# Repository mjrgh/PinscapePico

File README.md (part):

# 

Pinscape Pico is a comprehensive I/O controller for virtual pinball
cabinets, designed for the Raspberry Pi Pico RP2040.  It handles
nearly all of the common input and output functions in a virtual pin
cab: arcade-style pushbuttons and switches, accelerometer-based
nudging, mechanical plunger position sensing, and feedback effect
devices such as lights, shaker motors, fans, and solenoids.  It can be
used on a standalone Pico, and also with a wide range of peripheral
devices that expand the Pico's hardware capabilities: accelerometers,
PWM/LED driver chips, shift registers, GPIO expanders, ADCs, and
clock/calendar chips.  The project includes reference hardware designs for
several expansion boards that implement particular collections of
peripherals selected to meet the needs of most pin cab builders, and
all of the hardware interfaces are documented, so that you can design
your own custom boards if you prefer.

This project is a sequel to the original [Pinscape KL25Z controller](https://github.com/mjrgh/Pinscape_Controller),
but it's all new code, not a port of the KL25Z software.  The Pico is
a more powerful platform than the KL25Z, so I wanted to make a fresh
start to take advantage of the Pico's expanded capabilities.  Pinscape
Pico has all (I'm pretty sure) of the features of the original KL25Z
Pinscape, plus some neat new tricks.  It's a little more "technical"
than the KL25Z system, but also more powerful and flexible.

## Quick setup guide

A pre-built Windows installation is available on the github project page,
under the **Releases** section in the right panel.

The distribution is a ZIP file.  To install, just unpack the ZIP file
into a local directory on your hard disk.  Just about any folder
location will work, except that you should avoid any of the Windows
system folders and the C:\Program Files tree, since those folders
are protected.

Once you unpack the files, you can launch the Pinscape Pico GUI Config
Tool by double-clicking **GUIConfigTool.exe**.  That's designed to be
your main gateway to the system, and it'll display on-screen
instructions for setting up a new Pico with the Pinscape software.

[More setup details](#SetupDetails).

[Linux and MacOS versions](#linuxAndMac)

## What can you do with it?

Here are some examples of how you can set up a Pinscape Pico system.
There's a more comprehensive list of features a little later in this
article, but it might help to start with some more concrete examples
of what your overall system might look like.

* <b>Button controller:</b> A really simple way to use Pinscape is as
a button encoder, for connecting arcade pushbuttons to a PC.  The
Pico is the only piece of hardware you need for this (other than
the buttons), since you can connect the buttons directly to the Pico's
GPIO ports.  The Pico has a total of 26 external GPIO pins, so you can
connect up to 26 buttons.  Each button can be mapped to the PC as a
keyboard key, a gamepad button, or a variety of other options, and
the Pico responds to button presses within microseconds, for very small
latencies sending input to the PC.  (Pinscape can also handle many
more buttons than just 26 if you need more, but that gets a little
more complicated, because you have to add some external peripheral
chips to create more ports beyond the Pico's 26 built-in GPIO pins.)

* <b>Accelerometer-based nudge device:</b> A slightly more complex
setup adds an accelerometer, to detect when you nudge the cabinet, so
that the pinball simulator can apply the nudge force within the game.
Analog nudging adds a wonderful extra dimension to video pinball that
lets you interact with the game in a much more natural, physical way.
The Pico doesn't have a built-in accelerometer, so this setup
requires adding an external accelerometer.  But that's very easy
to do, thanks to breakout boards available from Adafruit, Sparkfun,
and others.  (A breakout board is a small circuit board with a
specific chip and all of the necessary supporting parts, fully
soldered and assembled, so all you need to do to connect it to a
Pico is run a few wires between the breakout board and the Pico
GPIO pins.)  I recommend the Adafruit MMA8451Q and LIS3DH boards
(MMA8451Q is the better choice in terms of sensor performance).
You can combine nudge input with button inputs, too, although this
will reduce the number of button ports to 24 (because the
accelerometer requires two GPIO ports for its own use).

* <b>Plunger:</b> You can also add a mechanical plunger position
sensor.  Apart from the plunger sensor itself, no other hardware
is needed.  The simplest plunger sensor type is a slide potentiometer,
which connects to the Pico with three wires.  You can combine this
with the accelerometer and button functions as well.

* <b>Feedback device controller:</b> Pinscape can act as a replacement
for the LedWiz and its competitors - devices that control a fixed set
of feedback devices, and do nothing else.  Pinscape can even emulate
the original LedWiz USB interface, if you want it to, which makes it
plug-and-play compatible with old LedWiz-based software.  To control
feedback devices, though, you need to add some custom external
hardware, because the Pico by itself can only control tiny amounts of
power, just enough for a small LED.  So you need "booster" (amplifier)
circuitry to control motors, solenoids, and bigger lights.  Pinscape
is flexible enough to work with a wide range of booster circuits, so
you can roll your own if you want, but you don't have to.  The
Pinscape Pico project includes several "reference" expansion board
designs, which are open-source circuit board layouts that anyone is
free to build on their own, or to customize to fit specific
requirements.

* <b>Comprehensive I/O controller:</b> The reference expansion boards
don't *just* control feedback devices.  They're designed as **all-in-one**
boards that handle just about everything you'd need in a full-featured pin
cab, including accelerometer, plunger, buttons, and feedback devices.
So you can combine the features of a button encoder, nudge device, and
feedback controller into a single Pico running Pinscape.

## Supported Pico versions

All of my development testing was done with a Raspberry Pi Pico RP2040
board.  There are numerous clones of the Pico available from different
vendors, but I haven't tested on any of those, so use those at your
own risk.  I don't mean to imply that other boards *won't* work, only
that I don't know one way or the other, since the only thing I've
actually tested against is the original Pico.  (There is one specific
problem that several people using unspecified clones have reported,
which is that saving configuration data to flash doesn't work on those
devices.  Since I've heard the same thing from a few people, it seems
to be a systematic problem with certain clones, but I don't know
specifically which devices are affected, since the clones are mostly
unbranded.  I don't know the cause of the problem, so if you run into
something like that with a clone, the only solution I can offer is to
switch to a genuine Raspberry Pi device.)

The release package also includes a build for the Raspberry Pi Pico2
RP2350.  The Pico 2 is a next-generation Pico with a new CPU, more
memory, and numerous upgrades to the on-board peripherals.  It looks
just like an original Pico, but it's really a whole new platform, and
it's not directly compatible - it requires a separate build.  Pinscape
support on Pico 2 is still experimental: I haven't tested it on the
Pico 2 beyond the basics, so there are probably some incompatibilities
yet to be found.  But reports so far have been that most features are
working as expected.  Note that there's no particular advantage to
running Pinscape on a Pico 2 over an original Pico, since the software
doesn't currently use any of the Pico 2's new features.

The Pico "W" variations (Pico W and Pico 2W) are **not supported** at
the moment.  The W's have somewhat different internal wiring to accommodate
the addition of the radio modules, and those wiring changes require some
corresponding software changes, which Pinscape doesn't provide.  Some
people have reported that Pinscape *mostly* works on the W; the only
problem reported so far is that the on-board LED doesn't work.  So you
can use a W if you can live with the LED not working, and with any
other problems that might still be lurking.  But I don't see any
reason you'd want to, because Pinscape can't take any advantage of
the W's wireless features.  You're better off using a regular Pico
for Pinscape, and saving the Pico W for an application that actually
uses the WiFi or Bluetooth features.

## Features

* USB keyboard emulation, for button input mapping

* USB gamepad emulation, for button inputs, accelerometer, and plunger

* XBox controller emulation ("XInput"), as an alternative to the HID gamepad
(and the controller's feedback features (LEDs and rumble motors) can be mapped to
output ports via the "computed output" feature)

* [Open Pinball Device](http://mjrnet.org/pinscape/OpenPinballDevice/OpenPinballDeviceHID.htm) support

* All input devices (keyboard, gamepad, XBox, Open Pinball Device) are optional, they can be mixed
and matched in any combination, and and all of their virtual controls (buttons,
joystick axes) can be individually mapped to whichever physical inputs you like
(physical buttons, accelerometer axes, plunger sensor)

* Support for PWM outputs directly through Pico GPIO ports, as well as
multiple external PWM output controller chips (TLC5940, TLC5947, TLC59116,
PCA9685), and even shift-register chips (74HC595)

* Gamma correction option for PWM output ports, with the gamma
calculated at the device's full resolution (e.g., 12-bit gamma scaling for
TLC5940, TLC5947, and PCA9685)

* Configurable "flipper logic" timer protection (in software) for all output ports

* Support for shift register output ports via 74HC595, which can be configured
as digital ON/OFF outputs or as PWM outputs

* Support for digital ON/OFF output ports via PCA9555 GPIO expander chips

* A companion project, "PWMWorker", turns additional Picos into 24-port
I2C PWM controllers, the equivalent of 1&half; TLC59116 or PCA9685
chips, but in the DIY-friendly Pico package, and at the DIY-friendly
Pico price point.  Add more PWM ports to your system, 24
at a time, without any SMD soldering.  
Details: [Data Sheet](http://mjrnet.org/pinscape/PWMWorker/DataSheet/PWMWorkerDataSheet.htm); [Project subtree](PWMWorker).

* Support for button inputs directly through Pico GPIO ports, as well as through
74HC165 shift registers and PCA9555 GPIO expanders

* Extremely low latency on GPIO and 74HC165 input ports (microseconds on the
device side, 1-2 milliseconds end-to-end delivery to the application through USB)

* Ports on PCA9555 chips can be individually assigned as button inputs ports and
feedback device output ports, freely mixing port types on the same chip

* An extensible design for all of the external hardware interfaces, to allow
new chips to be added in the future

* "Logical button" design that allows mapping multiple types of physical inputs to
multiple types of PC inputs and other actions, including keyboard keys, gamepad buttons,
IR remote control code transmissions, and internal actions such as engaging Night Mode
or firing an output port

* Button macros, to carry out a timed series of actions when a button (physical or logical) is pressed

* "Shift buttons", to allow mapping multiple functions to a single physical input; multiple
shift buttons can be defined, to allow for shift "chords" (analogous to PC key combinations like Shift+Ctrl+X)

* Short-press/long-press buttons, to map two functions to one button based on press time

* Native DOF support, via Pinscape Pico device recognition in DOF (present in unified R3++ DOF releases since late 2024)

* "Logical output port" design that allows mapping physical outputs to DOF ports, internal sources,
and "computed" sources that let you combine DOF ports, control multiple things with one DOF port,
control ports based on timed events or internal device events, and all sorts of other things

* Shared DOF output ports, for sharing a small number of physical feedback devices with a
larger set of virtual DOF ports, ideal for setting up a mini-cab with limited space

* Night Mode, to disable designated outputs as a group for quieter play

* Time-of-day features, and support for an external real-time clock (RTC) chip to keep time
while the power is off

* [LedWiz emulation](LedWizEmulationOptions.md), for legacy applications that access the LedWiz directly (rather than through DOF);

* IR remote control receiver/transmitter, with the full universal-learning-remote design from the KL25Z Pinscape

* The "TV ON" feature from the KL25Z Pinscape, with support for the same type of external power-sensing circuit,
and the same support for a TV Relay and IR command activation when a power-on transition occurs

* Plunger sensor support for all of the KL25Z Pinscape sensors, with the same plunger logic features

* Nudging, with support for multiple accelerometer chips (MMA8451Q, LIS3DH, LIS3DSH, MXC6655XA, MC3416, MPU-6050),
with an extensible design to allow support for more accelerometer chips to be added in the future

* Nudge Velocity input support for the latest Visual Pinball

* Plunger and accelerometer inputs can be mapped to any suitable gamepad axes, and can also be used
as inputs to logical buttons and logical output ports; for example, you can set up a button that
triggers when the accelerometer X axis exceeds a given threshold, or set up an LED that turns on
when the plunger is pulled

* Plunger Velocity input support for the latest Visual Pinball

* Extremely flexible configuration system, with practically all of the
hardware setup under user control, using the human-friendly JSON text file format

* Detailed error/status logging, viewable on the PC via UART (physical serial port), USB CDC (virtual COM port),
and the Config Tool, for easier troubleshooting

* A simple command console, accessible through UART and USB CDC ports, with access to internal
debugging and troubleshooting commands; mostly a debugging tool for developers, but possibly useful
for troubleshooting problems that don't easily yield to other means

* GUI configuration and testing tool, with detailed visualizations of hardware
and software status for button inputs, feedback device outputs, plunger sensor, and IR features

### Non-features (things Pinscape Pico doesn't do)

Pinscape Pico is billed as a "comprehensive" I/O controller for
virtual pinball cabinets, but there are a few I/O functions that
Pinscape doesn't handle.  In each case, the decision to omit them was
based primarily on the resource limits of the Pico: there would be too
many compromises trying to make a single Pico perform all of its
Pinscape duties *plus* these other tasks.  Fortunately, all of these
functions are already covered by other open-source projects that run
on similarly inexpensive hardware, so leaving them out of Pinscape
shouldn't be an obstacle to including them in a DIY pin cab.

* **No smart light strips:** Pinscape doesn't control smart light
strips - the kind with individually addressable RGB LEDs, such as
WS2812B strips.  The resource limit that makes this impractical to
include in Pinscape is the Pico's relatively small number of GPIO
ports.  For a typical pin cab light strip setup, you'd need four to
eight GPIO ports dedicated to the light strips.  Pinscape needs almost
all of the GPIO ports to itself as it is.

* **No Dot-Matrix Displays (DMDs):** Pinscape also doesn't control the
128x32 dot-matrix display panels found in 1990s pinball machines, and
still popular in virtual pinball cabinets.  The main reason to
dedicate a separate controller to the DMD is that it requires a lot of
USB bandwidth, since the DMD is essentially a small video display.  A
separate device with its own USB port is the simplest way to ensure
plenty of bandwidth for everyone.

## Documentation

The documentation is a little thin so far, since I haven't yet updated
the [Pinscape Build Guide](http://mjrnet.org/pinscape/BuildGuideV2/BuildGuide.php)
to cover the Pico system.  A lot of the general pin cab material in the Build
Guide still applies equally well to Pinscape Pico, since most of it isn't at all
tied to the KL25Z or the original Pinscape software.  But the Build Guide also
has a lot of material that's specifically about how to build and set up the
original Pinscape KL25Z system, and so far I haven't written anything equivalent
for the new Pico software.

Here's what's I do have:

<b>[JSON Configuration Reference](http://mjrnet.org/pinscape/PinscapePico/Help/JSONConfigRef.html):</b>
This has the most comprehensive documentation on the firmware's
workings currently available.  It's in reference format, so it's
not a very good tutorial, but each of the major features has an
introductory section that explains how it works, including wiring
guides for most of the supported peripheral hardware devices.
    
When you're using the configuration editor in the Config Tool, the
editor keeps track of your editing location, and can take you straight
to the reference section on the topic you're currently editing.
At the upper right corner of the editor window, there's a link showing
the current JSON element, which automatically updates to match the
JSON at the text cursor position.  Click the link to open the
reference section for the current JSON element.

<b>[Config Tool help](http://mjrnet.org/pinscape/PinscapePico/Help/ConfigTool.htm):</b>  This documents the Config Tool in detail.
It's built into the Config Tool UI, and is also available online.

<b>[LIS3DH setup guide](Guides/LIS3DH-Setup.md):</b>  A tutorial guide
to setting up a LIS3DH accelerometer with a standalone Pico.  This will
probably be the most common initial setup for people who don't need the
Expansion Boards, so I wrote this guide to help get started.

## LED Status Codes

The Pico has a small green LED on top, which the Pinscape software uses
as a very coarse status indicator.  When everything is running properly,
the LED flashes slowly, about one second on and one second off.  When
the USB connection is interrupted, such as when the host PC is in sleep
mode, the LED shows a very short flash about every two seconds.  If the
LED isn't flashing at all (either stuck on or stuck off), the software
isn't working properly.

<b>Expansion board RGB:</b> If you're using one of the Expansion
Board designs, the board features a full-color RGB LED, which the
software uses to display a slightly more detailed status indication:

* Slow alternating Blue/Green: connected, running properly, plunger sensor calibrated (or no plunger configured)

* Slow alternating Green/Yellow: connected, running properly, plunger sensor not yet calibrated

* Two short yellow flashes every two seconds: waiting for host PC to establish the USB connection

* Two short red flashes every two seconds: USB connection interrupted (cable disconnected or data/protocol error communicating with the PC)

* One short green flash every two seconds: host PC is in sleep mode

* Blue on/off every half second: TV ON countdown in progress after system powered on

* Fast Blue flashes: TV ON feature is transmitting IR commands

* Fast alternating Red/Orange: Safe Mode is in effect

* Slow alternating Green/Dim Green: Factory Reset mode is in effect

* Solid Blue: Plunger calibration is in progress

* Fast Blue flashes: Plunger calibration button is being pressed (keep holding to activate calibration)

* Solid Violet: Nudge noise level calibration is in progress

## More details on installation

### Initial Pico firmware installation

The Pinscape Pico Config Tool guides you through the initial setup process for a new
device.  Just run the program and follow the on-screen instructions under the "New
Device Setup" section.

If you prefer to carry out the steps manually, without the Config Tool involved,
you can also use the standard, native Boot Loader procedure you'd use with any Pico
software:

* Unplug your Pico from USB (and all other power sources)

* Press **and hold** the button on top of the Pico while plugging it in, then release the button

* You should see the Pico appear on your Windows desktop as a virtual thumb drive

* Drag and drop **PinscapePico-pico.uf2** from the Pinscape folder onto the Pico virtual disk
(or use a COPY command in a DOS box)

The Pico should now automatically reboot into the Pinscape software.  If the
software is working properly, the little green LED on top of the Pico will
blink at about 1 Hz, and the device should appear as a Pinscape Pico unit
in the Config Tool.

After the initial install, you can install firmware updates directly
through the Config Tool without all of the manual steps.

### Configuration

This project's configuration setup is rather different from the KL25Z
Pinscape setup.  Instead of a graphical config tool, Pinscape Pico
uses a text file written in the widely-used JSON format.

The JSON file format and contents are documented in the Config Tool
help.  The Config Tool features an integrated text editor (based on
Scintilla) with JSON syntax-aware coloring and indenting, and
quick linking from the current editing location (based on live
syntax scanning) to the relevant documentation.

When you first fire up the GUI Config Tool and go to the Main
Configuration view, the program will offer a choice of initial
template configurations that you can use as a starting point.
The templates contain many examples of common configuration
elements, commented out, that you can un-comment and edit as
needed to add to your own configuration.

Alternatively, you can also send a config file to the Pico using the
command-line Config Tool, from a DOS box:

`ConfigTool --put-config MyConfig.json --reset`

Replace `MyConfig.json` with the actual name of your JSON file.  The
`--put-config` part installs your JSON file on the device.  The new
settings don't go into effect until you reboot the device, which is
why we also added `--reset` at the end.

### Linux and MacOS

A Pico running Pinscape can be plugged into a Linux or MacOS host just
as well as a Windows host, but that leaves the question of how you
configure it.  The original GUI Config Tool that's part of this
repository only runs on Windows, but fortunately, there are a couple
of options for Linux and MacOS users.

<b>Pinscape Cross:</b>
The best option is [Pinscape Cross](https://github.com/superhac/pinscape-cross/),
by superhac.  Pinscape Cross is an independent, full-featured implementation of
the GUI Config Tool that runs on Windows, Linux, and MacOS.

https://github.com/superhac/pinscape-cross/

<b>Linux command-line tool:</b>
In addition, there's a Linux version of the original command-line
Config Tool available.  You can build it via the shell script `./build_linux.sh`,
under [CmdLineConfigTool/Linux/](CmdLineConfigTool/Linux/).  Once that's built,
you can install a config file on the Pico with this command:

`./pinscape-config --put-config MyConfig.json --reset`

The command-line tool only has a subset of the functionality of the
GUI versions, but it can handle most of the core setup operations.
Its big limitation is that it doesn't have any of the interactive
visualization and testing tools that the GUI versions have, so it's
not as helpful for testing and troubleshooting.

### Firmware updates

You can update the firmware using the same procedure as the initial
install, by forcing the Pico into Boot Loader mode via the BOOTSEL
button and manually copying the new UF2 file.

But there's also an easier way.  Once Pinscape is installed, the
Config Tool can install firmware updates for you with a couple of
mouse clicks, with no need to physically unplug the Pico or fuss with
the BOOTSEL button.

In the GUI config tool, the main Overview window has controls for
updating the firmware.

To update the firmware from a DOS box, use the command-line config tool:

`ConfigTool --update PinscapePico-pico.uf2`

That automatically places the Pico into Boot Loader mode, copies
the specified UF2 file into its flash, and reboots the Pico to
launch the updated firmware.

## Safe Mode

Pinscape uses the Pico's hardware watchdog module to automatically
detect most software crashes.  The watchdog is essentially a hardware
timer that performs a power-cycle reboot on the Pico if the software
ever stops responding for more than a fraction of a second.  This is
an excellent way to detect software crashes, freezes, and other
problems that make the software stop functioning correctly, and in
most cases, it prevents the Pico from ever getting into a truly
unresponsive state.

When the hardware watchdog detects a crash, it reboots Pinscape into
Safe Mode.  Safe Mode runs the normal Pinscape firmware, but it
bypasses the usual JSON configuration file, and instead uses a
stripped-down configuration with a minimal number of features enabled.
The idea is that most crashes are caused by specific features in the
software, rather than by the core system software, so disabling most
of the optional features will allow the basic core software to run
without problems.

When Safe Mode is active, the Config Tool can connect to the Pico, and
you can inspect and edit the JSON configuration file.  You can also
use Safe Mode to install new firmware, if you're aware of a newer
firmware version that contains a fix for the crash.

If you suspect that the crash that led to Safe Mode activation was due
to a particular feature, you can use Safe Mode to edit the
configuration file and disable the suspect feature.  If you think it
was due to a setting, but you're not sure which one, you can
experiment with disabling features until you find the one responsible.

If you think the crash was purely random or sporadic, you can just
reboot the Pico and try again.  If the Pico keeps going back into Safe
Mode after each reboot, you probably will need to disable something in
the configuration to get back to normal operation.

By default, Safe Mode uses default "factory" settings for everything.
You can optionally create your own Safe Mode configuration file via
the Config Tool, in the Safe Mode Config window.  This works exactly
like the regular JSON configuration; it's just a separate JSON file
that's loaded instead of the regular one when Safe Mode is triggered.
The Safe Mode config file lets you enable specific features even when
in Safe Mode.  Naturally, you should minimize the features you enable
here, since the whole point is to create a minimal configuration that's
less likely to crash specifically because it doesn't enable many features.
I like to configure the ID information here to match the main configuration,
and also enable the UART ports, so that I can access the command console
for troubleshooting even when Safe Mode is active.

## Recovering a bricked Pico

First, you can't actually "brick" a Pico, in the sense of rendering it
permanently unrecoverable due to a software error.  But the Pinscape
software certainly can crash, and it can crash at startup, such that
it won't connect to the Config Tool long enough to let you perform an
update.  So the Pico might *appear* to be bricked.  Even this is
unlikely, because the Pico will automatically detect most crashes
and reboot itself into Safe Mode (see above), giving you access to
basic configuration functions.

In the event that Safe Mode doesn't kick in, it's *still* essentially
impossible to truly brick a Pico, thanks to the Pico's boot loader
being etched into inalterable hardware ROM.  No matter how badly the
software screws up, there's just no physical way that it can break
the ROM.  If the Pinscape software ever makes your Pico appear unresponsive,
you can always restore it to Boot Loader condition as follows:

* Disconnect the Pico from USB (and any other power sources)

* Press **and hold** the BOOTSEL button on top of the Pico while plugging in the USB cable

Holding the BOOTSEL button during a power cycle activates the Pico
boot loader, bypassing any software loaded in flash.  Since it's
impossible to erase the boot loader program itself (as it's stored in
unerasable ROM), and since the BOOTSEL button physically bypasses the
flash during the reset, there's nothing that a firmware program can do
to prevent this assertion of Boot Loader control, even if it were
deliberately trying to.

After you perform the BOOTSEL maneuver, the Pico should appear as a
virtual thumb drive on your Windows desktop.  You can now replace the
flash firmware by dragging the new .UF2 onto the Pico thumb drive.

For most programs, it would be enough at this point to reinstall the
firmware.  However, that's not necessarily good enough with Pinscape,
because Pinscape *also* stores your configuration file in the Pico's
flash memory, in a separate area from the program executable.  You
can fully reset the Pico to factory conditions using the Config
Tool, via the Device menu on the main Overview page, or via the
Boot Loader view, if the device is currently in Boot Loader mode.

## Expansion boards

Pinscape Pico will work on a completely stand-alone Pico, but for
a full virtual pin cab setup, you'll almost certainly want to add
some external peripherals to supplement the Pico's relatively
small complement of GPIO ports, and its lack of an on-board
accelerometer.

As part of the Pinscape Pico project, I've developed a few custom
"expansion boards" purpose-built for virtual pin cabs.  They're
all open-source designs that anyone can build; you can find the
EAGLE layouts in the [ExpansionBoards](ExpansionBoards) folder.

* **DIY-friendly expansion board set:**  A two-board set, designed
  to work together as a unit, providing a complete virtual pin cab
  I/O controller powerful enough for a high-end build with just
  about every toy known.  "DIY-friendly" means that it's designed
  entirely from parts that are easy to source and easy to solder
  by hand - it's meant to be something you can build yourself.

* **"Pro" expansion board:** An all-in-one board with a similar
  set of features to the DIY-friendly set, just with everything
  packed into a single board, thanks to the higher density made possible
  by fine-pitch SMD parts.  I call it the "Pro" board not because
  it's any better than the DIY board, but just because it's not the
  sort of thing most people would *want* to build by hand, thanks
  to the use of small SMD parts.  It's really only practical to assemble
  robotically, and that probably means that it will only be economical
  to produce in moderately large batches, like tens or hundreds or units.
  I expect that this will be an obstacle to DIYers, but one of our
  enterprising community members who's set up for retail sales might
  be able to build them and offer them for sale.  But even so, the
  "pro" isn't for "proprietary" - it's still an open-source design
  that you can build yourself, provided you have the means to work
  with the small SMD parts involved.

* **KL25Z adapter:** An adapter board that makes the Pico mimic
  a KL25Z, for use with the original Pinscape KL25Z expansion boards.
  This is designed for people that already have the KL25Z boards,
  and want to keep using them, but also want to upgrade to the new
  Pico software.  This is designed as a drop-in replacement for the
  KL25Z in your old setup.

But Pinscape Pico isn't limited to *my* expansion board designs.
The software was designed from the ground up to be fully configurable,
and has support for numerous peripheral options.  It doesn't make any
assumptions about which peripheral devices are present.  It'll work
just as well with other people's expansion board designs as with my
board designs.

## How to build the project from source code

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
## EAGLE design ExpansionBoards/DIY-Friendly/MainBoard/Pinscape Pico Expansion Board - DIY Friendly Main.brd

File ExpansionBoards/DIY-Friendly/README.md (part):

# Pinscape Pico - DIY-Friendly Expansion Board

This is an EAGLE design for a two-board expansion set for the Pinscape
Pico software.  Pinscape Pico is firmware for the Raspberry Pi Pico
that turns a Pico into a highly customizable I/O controller for
virtual pinball cabinets.

## Description

This board set is my second Pinscape Pico expansion board design.  The
first is an All-In-One board that packs everything you need for a
well-equipped pin cab onto one 10x16 cm board.  To achieve that kind
of density, that design uses tiny SMD (surface-mount) parts for just
about everything, some of which are too small even to handle with
tweezers.  It's not something you want to assemble by hand, unless
your other hobby is building Swiss watches from scratch; it's really
only feasible to build in a factory with a pick-and-place machine.
That's only cost-effective if you're going to order at least 50 or 100
units, so I expect that the all-SMD board will only be of interest to
our more entrepreneurially-minded community membe who might be
willing to order up a batch and offer them for retail sale.  That's
why I've taken to referring to that design as the "Pro" expansion
board.

But Pinscape has always been for DIYers.  My mission from the start
has been to make it possible to build high-end pin cabs without
depending on commercial devices, since we're such a niche hobby that
it's hard to get most commercial vendors to take us seriously as
customers.  So I didn't like the idea of only having a "Pro" design; I
also wanted to provide a DIY-friendly design that works with the new
software.  That meant designing another board using only parts that
are easy to solder by hand.

The result is this two-board expansion set.  It outfits the Pico with
a large set of physical input and output connections that let you
connect just about everything you'd find in a top-of-the-line pin cab,
from button inputs to feedback device outputs.  It has two main
design goals:

* It's comprehensive: it provides the extra peripherals required for
all of the Pinscape features (accelerometer, plunger input, button
input, feedback device control, IR remotes, TV ON power sensing), and
has ample button and feedback device ports to wire a fully decked out
pin cab

* It's DIY-friendly: it includes only through-hole parts that can
be easily soldered by hand

A third, lesser-but-still-important priority is to use common parts
that are widely available and are likely to remain in production for
many years.  The original Pinscape KL25Z boards are difficult to build
today because they depend on a few specific parts that are no longer
in production, most especially the KL25Z itself, but also the
TLC5940NT PWM chips.  I tried to avoid those sorts of dependencies as
much as possible in this design.  The biggest unique-part dependency
is the Pico itself, which is widely available and well supported by
Raspberry Pi.

Unlike the original Pinscape KL25Z expansion boards, where you were
encouraged to mix and match the Main, Power, and Chime boards in
different combinations to come up with a bespoke port layout, this
board set is designed as a One-Size-Fits-All solution.  There's no
provision to add a second or third power board, and there aren't any
optional add-on boards comparable to the Chime board.  The goal is
that the two boards have enough general-purpose ports between them
that no one would even want to add a third board - the two boards
should cover just about everything in a full-featured pin cab.

You can, however, use the main board all by itself.  I tried to
arrange things so that almost everything is on the main board, except
for the bulk of the output ports.  And even then, the main board has a
fair number of outputs.  If you use the main board on its own, you
still get the 16 flasher/strobe ports and 12 of the high-current MOSFET
outputs, plus all of the other I/O functions (buttons, accelerometer,
plunger connections, IR remote, TV ON).  The second board just adds 16
more high-current MOSFET outputs and the 32 mid-power lamp outputs,
plus the real-time clock chip, which most people won't especially miss.
If you don't need all of the extra output ports or the RTC, the main
board makes a perfectly good stand-alone controller.

My reason for using a less "modular" design than the old boards is
that I think the modularity ended up being a net negative: it added
flexibility, but at the cost of more complexity.  And I don't think
very many people took advantage of the flexibility - I think
practically everyone built one of the "standard" configurations,
either the Main + Power board combo, or a Main + Power + Chime set.
But everyone still had to go through the process of planning their
setup and then customizing their configuration settings once it was
built.  This time around, I figured that if everyone's going to build
the standard configuration anyway, let's make the standard configuration
so comprehensive that no one would really need other options.  It
simplifies the design, and it simplifies everyone's planning and
setup process.

## Features

* 32 button inputs, using shift register chips for extremely low latency
scans (order of 10 microseconds)

* Accelerometer (LIS3DH), installed via a pre-assembled module
available from Adafruit (no need to hand-solder the tiny SMD chip),
for nudge sensing

* An optional ADC (analog-to-digital converter, ADS1115), installed
via a pre-assembled module available from Adafruit, for high-precision
analog input from a potentiometer-based plunger (improving on the Pico's
mediocre built-in ADC)

* 28 MOSFET outputs for high-current feedback devices, such as motors,
solenoids, and standard LED strips

* 16 flasher/strobe ports for high-current LEDs, up to 1A per port,
for driving the 3W RGB LEDs typically used for flasher panels plus
a strobe LED

* 32 medium-current ports, up to 500mA per port, for driving almost
any sort of lamp (small incandescent or LED bulbs like those used in
lighted pushbuttons, small LEDs, large LEDs), relays and contactors,
and anything else that runs on less than 500mA

* All output ports have full PWM control, with configurable PWM
frequencies up to 65000 Hz

* Plunger input port, pin-compatible with the original Pinscape KL25Z
plunger port; just plug in your existing Pinscape plunger

* IR transmitter and receiver, with the sensor and transmitter on
small separate boards (connected to the main board with cables), so
that can be positioned anywhere in (or outside) the cabinet, to place
them in line-of-sight with the devices they're communicating with

* Power-sensing circuit for the Pinscape TV ON function (to help you
implement seamless one-button startup of the whole pin cab, even when
using TVs that don't remember their power state)

* Real-time clock/calendar chip with battery backup, for time-keeping
across Pico resets, even when the board is unpowered

## Board Design Files

Each board set consists of two sub-boards, titled **Main** and **Power**.
These two boards are designed to work together as a set.

Each sub-board design is contained in a pair of EAGLE files: **.sch** is the schematic,
and **.brd** is the physical board layout file.

The **.sch** file is a schematic, which is a special symbolic language
that electrical engineers use to describe the connections between
components in a circuit.  The symbology is more or less standardized,
so anyone with a basic knowledge of electronics should be able to read
it.  The schematic doesn't have any details on how the parts are laid
out physically, so it can't be used by itself to manufacture a board.
It's primarily for use by humans, to understand how the board works at
the electronic level.

The **.brd** file represents the complete physical layout of the
board.  This implements the same abstract network of connections
contained in the schematic, but it adds full details on the exact
physical placement of each component, and the layout of the copper
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
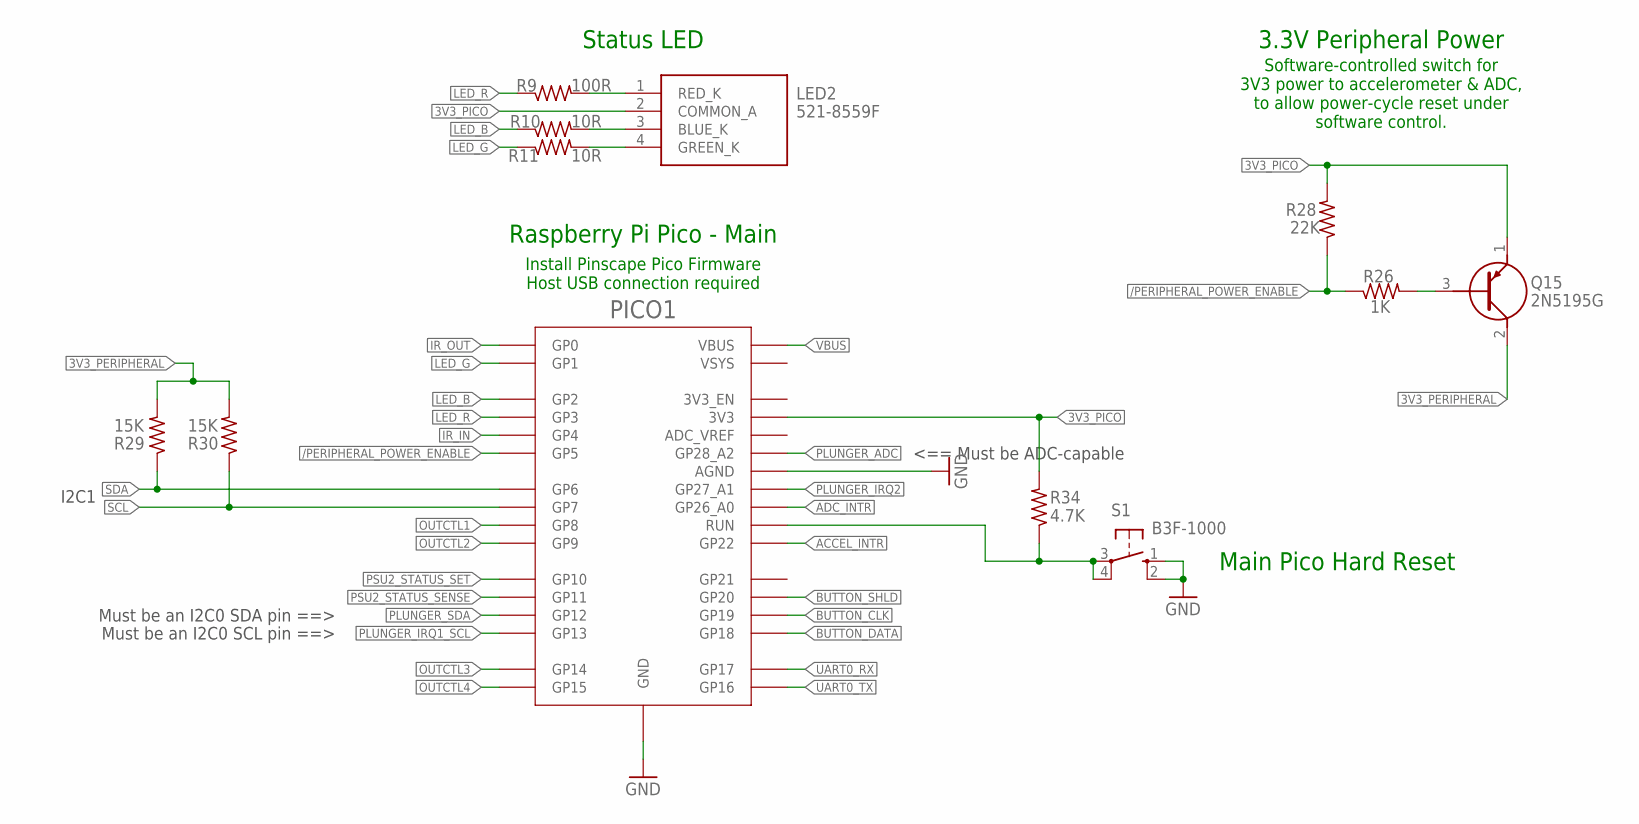
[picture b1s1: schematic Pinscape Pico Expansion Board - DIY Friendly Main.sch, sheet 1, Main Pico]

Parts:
LED2: 521-8559F; 5218559F
PICO1: RPI_PICO_NO_DEBUG; RPI_PICO_TH_NO_DEBUG
Q15: 2N5195G; TO229P300X760X1364-3P
R9: 100R; 0204/7; PARTNO MFR-12FTE52-100R
R10, R11: 10R; 0204/7; PARTNO MFR25SFTE52-10R
R26: 1K; 0204/7; PARTNO MF0204FTE52-1K
R28: 22K; 0204/7; PARTNO 660-MFS1/4DCT52R47R0
R29, R30: 15K; 0204/7; PARTNO MFR25SFRF52-15K
R34: 4.7K; 0204/7; PARTNO 660-MFS1/4DCT52R47R0
S1: B3F-1000; B3F-10XX

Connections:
3V3_PERIPHERAL: Q15.2 (C), R29.2, R30.2; also elsewhere on the board
3V3_PICO: LED2.2 (COMMON_A), PICO1.3V3, Q15.1 (E), R28.2, R34.2; also elsewhere on the board
/PERIPHERAL_POWER_ENABLE: PICO1.GP5, R26.1, R28.1; also elsewhere on the board
ACCEL_INTR: PICO1.GP22; also elsewhere on the board
ADC_INTR: PICO1.GP26_A0; also elsewhere on the board
BUTTON_CLK: PICO1.GP19; also elsewhere on the board
BUTTON_DATA: PICO1.GP18; also elsewhere on the board
BUTTON_SHLD: PICO1.GP20; also elsewhere on the board
GND: PICO1.AGND, PICO1.GND@1 (GND), PICO1.GND@2 (GND), PICO1.GND@3 (GND), PICO1.GND@4 (GND), PICO1.GND@6 (GND), PICO1.GND@7 (GND), PICO1.GND@8 (GND), S1.1 (S), S1.2 (S1); also elsewhere on the board
IR_IN: PICO1.GP4; also elsewhere on the board
IR_OUT: PICO1.GP0; also elsewhere on the board
LED_B: PICO1.GP2, R10.1
LED_G: PICO1.GP1, R11.1
LED_R: PICO1.GP3, R9.1
unnamed: LED2.1 (RED_K), R9.2
unnamed: Q15.3 (B), R26.2
unnamed: PICO1.RUN, R34.1, S1.3, S1.4 (P1)
unnamed: LED2.3 (BLUE_K), R10.2
unnamed: LED2.4 (GREEN_K), R11.2
OUTCTL1: PICO1.GP8; also elsewhere on the board
OUTCTL2: PICO1.GP9; also elsewhere on the board
OUTCTL3: PICO1.GP14; also elsewhere on the board
OUTCTL4: PICO1.GP15; also elsewhere on the board
PLUNGER_ADC: PICO1.GP28_A2; also elsewhere on the board
PLUNGER_IRQ1_SCL: PICO1.GP13; also elsewhere on the board
PLUNGER_IRQ2: PICO1.GP27_A1; also elsewhere on the board
PLUNGER_SDA: PICO1.GP12; also elsewhere on the board
PSU2_STATUS_SENSE: PICO1.GP11; also elsewhere on the board
PSU2_STATUS_SET: PICO1.GP10; also elsewhere on the board
SCL: PICO1.GP7, R30.1; also elsewhere on the board
SDA: PICO1.GP6, R29.1; also elsewhere on the board
UART0_RX: PICO1.GP17; also elsewhere on the board
UART0_TX: PICO1.GP16; also elsewhere on the board
VBUS: PICO1.VBUS; also elsewhere on the board

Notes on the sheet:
Raspberry Pi Pico - Main
Must be an I2C0 SCL pin ==>
<== Must be ADC-capable
Must be an I2C0 SDA pin ==>
Main Pico Hard Reset
Status LED
3.3V Peripheral Power
Install Pinscape Pico Firmware Host USB connection required
I2C1
Software-controlled switch for 3V3 power to accelerometer & ADC, to allow power-cycle reset under software control.

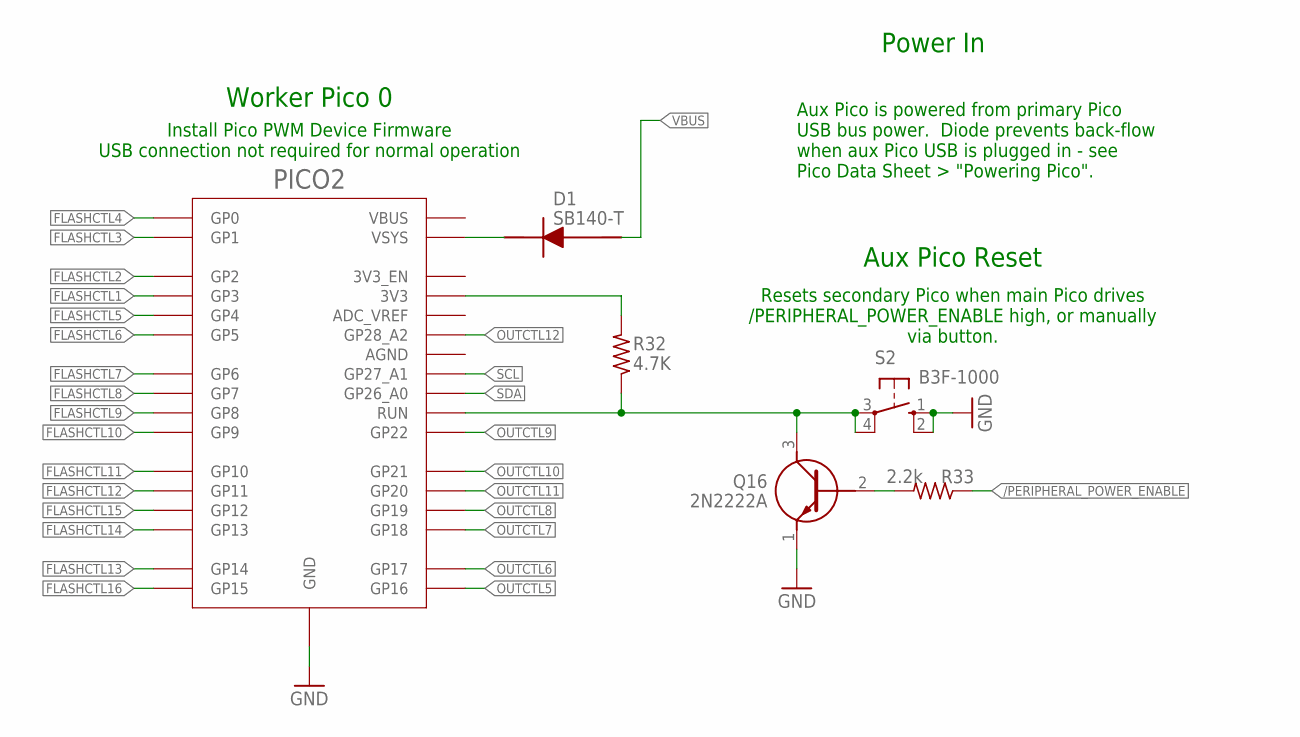
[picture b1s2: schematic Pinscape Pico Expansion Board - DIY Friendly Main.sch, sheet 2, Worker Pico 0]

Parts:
D1: SB140-T; DIOAD1408W86L464D236
PICO2: RPI_PICO_NO_DEBUG; RPI_PICO_TH_NO_DEBUG
Q16: 2N2222A
R32: 4.7K; 0204/7; PARTNO 660-MFS1/4DCT52R47R0
R33: 2.2k; 0204/7; PARTNO 660-MFS1/4DCT52R47R0
S2: B3F-1000; B3F-10XX

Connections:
/PERIPHERAL_POWER_ENABLE: R33.1; also elsewhere on the board
FLASHCTL1: PICO2.GP3; also elsewhere on the board
FLASHCTL2: PICO2.GP2; also elsewhere on the board
FLASHCTL3: PICO2.GP1; also elsewhere on the board
FLASHCTL4: PICO2.GP0; also elsewhere on the board
FLASHCTL5: PICO2.GP4; also elsewhere on the board
FLASHCTL6: PICO2.GP5; also elsewhere on the board
FLASHCTL7: PICO2.GP6; also elsewhere on the board
FLASHCTL8: PICO2.GP7; also elsewhere on the board
FLASHCTL9: PICO2.GP8; also elsewhere on the board
FLASHCTL10: PICO2.GP9; also elsewhere on the board
FLASHCTL11: PICO2.GP10; also elsewhere on the board
FLASHCTL12: PICO2.GP11; also elsewhere on the board
FLASHCTL13: PICO2.GP14; also elsewhere on the board
FLASHCTL14: PICO2.GP13; also elsewhere on the board
FLASHCTL15: PICO2.GP12; also elsewhere on the board
FLASHCTL16: PICO2.GP15; also elsewhere on the board
GND: PICO2.GND@1 (GND), PICO2.GND@2 (GND), PICO2.GND@3 (GND), PICO2.GND@4 (GND), PICO2.GND@6 (GND), PICO2.GND@7 (GND), PICO2.GND@8 (GND), Q16.1 (E), S2.1 (S), S2.2 (S1); also elsewhere on the board
unnamed: D1.1 (K), PICO2.VSYS
unnamed: Q16.2 (B), R33.2
unnamed: PICO2.3V3, R32.2
unnamed: PICO2.RUN, Q16.3 (C), R32.1, S2.3, S2.4 (P1)
OUTCTL5: PICO2.GP16; also elsewhere on the board
OUTCTL6: PICO2.GP17; also elsewhere on the board
OUTCTL7: PICO2.GP18; also elsewhere on the board
OUTCTL8: PICO2.GP19; also elsewhere on the board
OUTCTL9: PICO2.GP22; also elsewhere on the board
OUTCTL10: PICO2.GP21; also elsewhere on the board
OUTCTL11: PICO2.GP20; also elsewhere on the board
OUTCTL12: PICO2.GP28_A2; also elsewhere on the board
SCL: PICO2.GP27_A1; also elsewhere on the board
SDA: PICO2.GP26_A0; also elsewhere on the board
VBUS: D1.2 (A); also elsewhere on the board

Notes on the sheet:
Install Pico PWM Device Firmware USB connection not required for normal operation
Worker Pico 0
Aux Pico Reset
Resets secondary Pico when main Pico drives /PERIPHERAL_POWER_ENABLE high, or manually via button.
Aux Pico is powered from primary Pico USB bus power. Diode prevents back-flow when aux Pico USB is plugged in - see Pico Data Sheet > "Powering Pico".
Power In

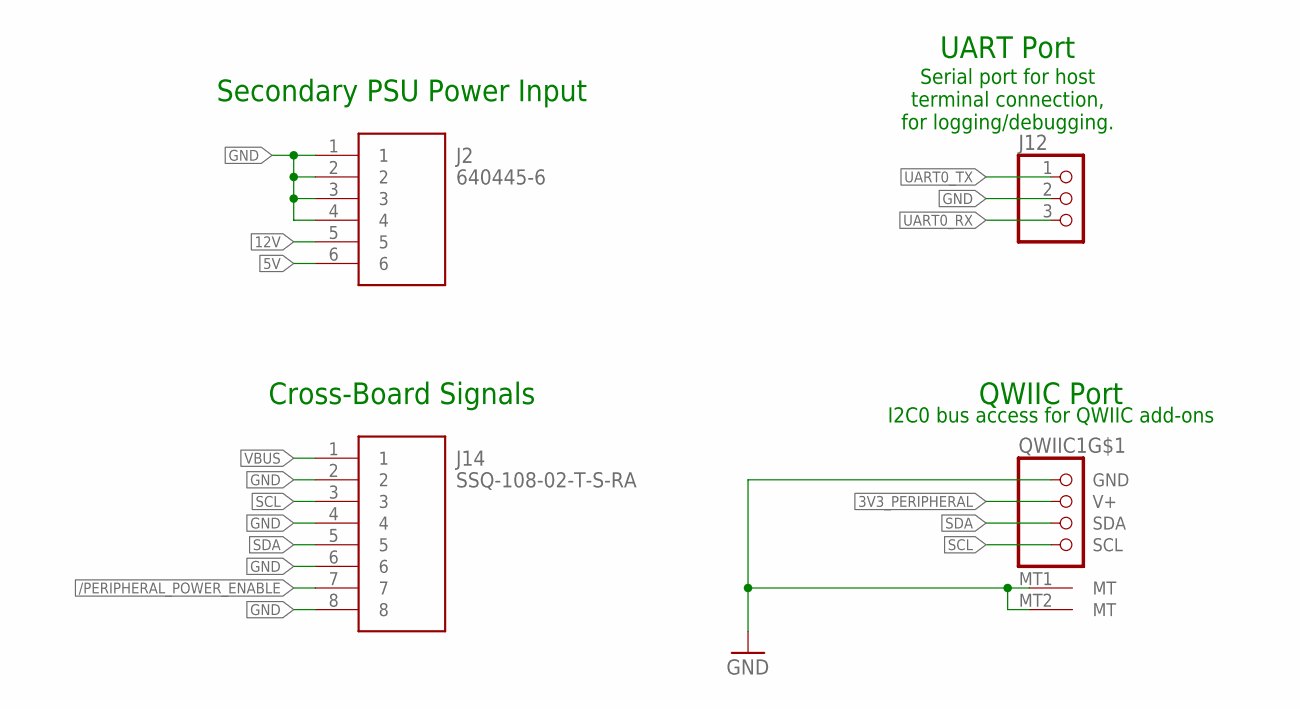
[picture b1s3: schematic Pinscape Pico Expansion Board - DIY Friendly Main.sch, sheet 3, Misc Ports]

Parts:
J2: 640445-6; SHDR6W183P0X396_1X6_2377X762X1
J12: PINHD-1X3; 1X03
J14: SSQ-108-02-T-S-RA; RHDRRA8W64P254_1X8_2083X851X24
QWIIC1: QWIIC; JST_SH4

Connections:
3V3_PERIPHERAL: QWIIC1.2 (V+); also elsewhere on the board
5V: J2.6; also elsewhere on the board
12V: J2.5; also elsewhere on the board
/PERIPHERAL_POWER_ENABLE: J14.7; also elsewhere on the board
GND: J2.1, J2.2, J2.3, J2.4, J12.2, J14.2, J14.4, J14.6, J14.8, QWIIC1.1 (GND), QWIIC1.MT1 (MT), QWIIC1.MT2 (MT); also elsewhere on the board
SCL: J14.3, QWIIC1.4 (SCL); also elsewhere on the board
SDA: J14.5, QWIIC1.3 (SDA); also elsewhere on the board
UART0_RX: J12.3; also elsewhere on the board
UART0_TX: J12.1; also elsewhere on the board
VBUS: J14.1; also elsewhere on the board

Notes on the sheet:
UART Port
Serial port for host terminal connection, for logging/debugging.
Secondary PSU Power Input
Cross-Board Signals
QWIIC Port
I2C0 bus access for QWIIC add-ons

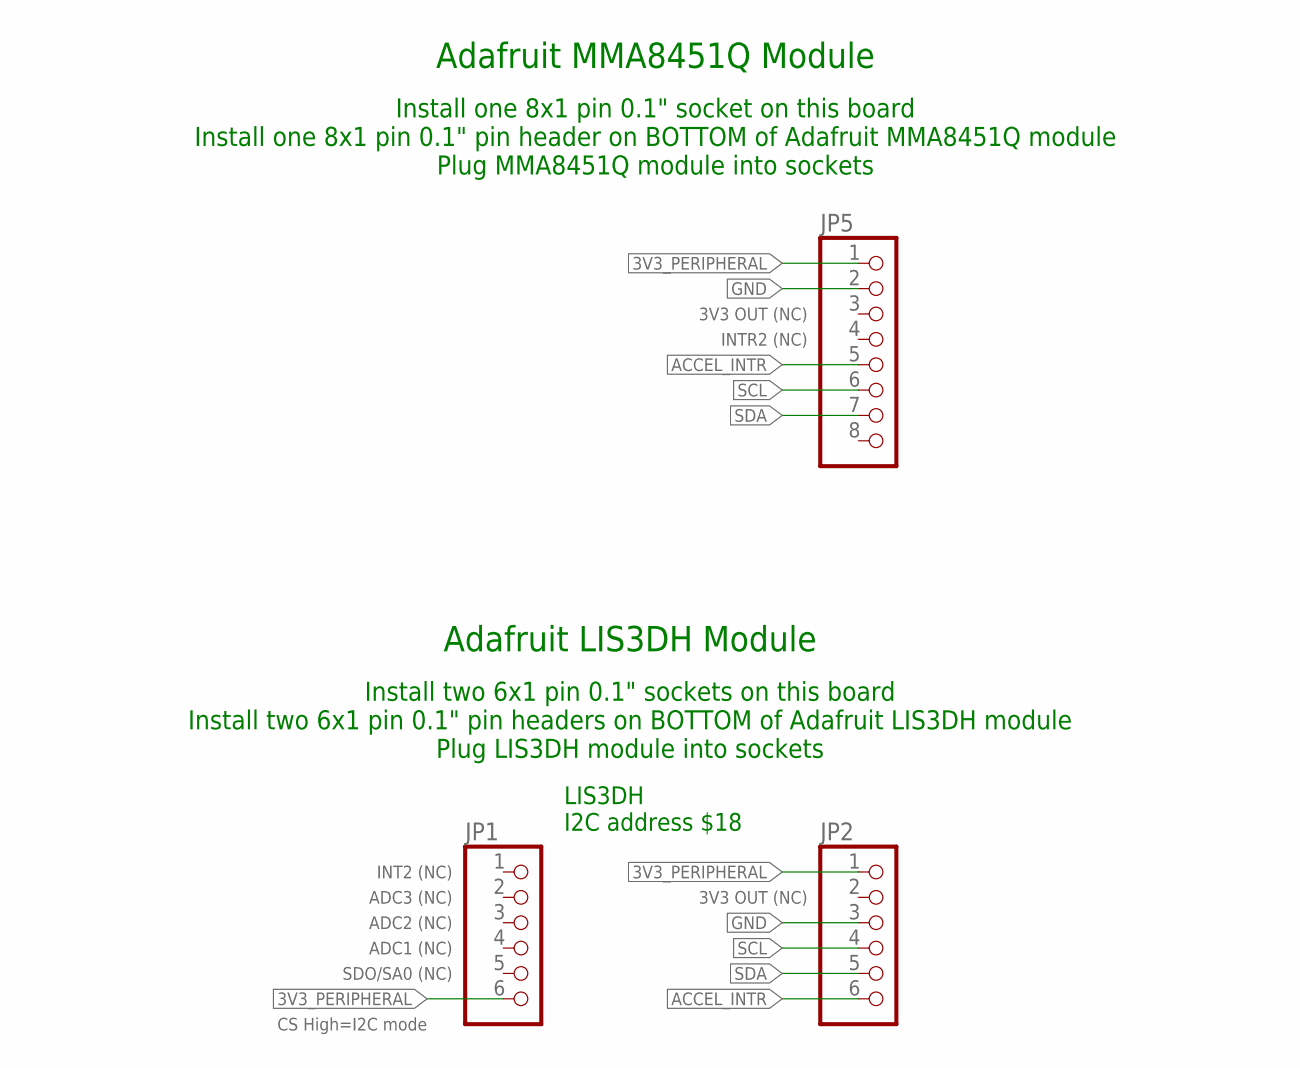
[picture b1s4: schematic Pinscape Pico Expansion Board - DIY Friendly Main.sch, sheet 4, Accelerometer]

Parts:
JP1, JP2: PINHD-1X6; 1X06
JP5: PINHD-1X8; 1X08

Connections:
3V3_PERIPHERAL: JP1.6, JP2.1, JP5.1; also elsewhere on the board
ACCEL_INTR: JP2.6, JP5.5; also elsewhere on the board
GND: JP2.3, JP5.2; also elsewhere on the board
SCL: JP2.4, JP5.6; also elsewhere on the board
SDA: JP2.5, JP5.7; also elsewhere on the board

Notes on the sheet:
Adafruit LIS3DH Module
Install two 6x1 pin 0.1" sockets on this board Install two 6x1 pin 0.1" pin headers on BOTTOM of Adafruit LIS3DH module Plug LIS3DH module into sockets
INT2 (NC)
ADC3 (NC)
ADC2 (NC)
ADC1 (NC)
SDO/SA0 (NC)
3V3 OUT (NC)
LIS3DH I2C address $18
CS High=I2C mode
Adafruit MMA8451Q Module
Install one 8x1 pin 0.1" socket on this board Install one 8x1 pin 0.1" pin header on BOTTOM of Adafruit MMA8451Q module Plug MMA8451Q module into sockets
INTR2 (NC)

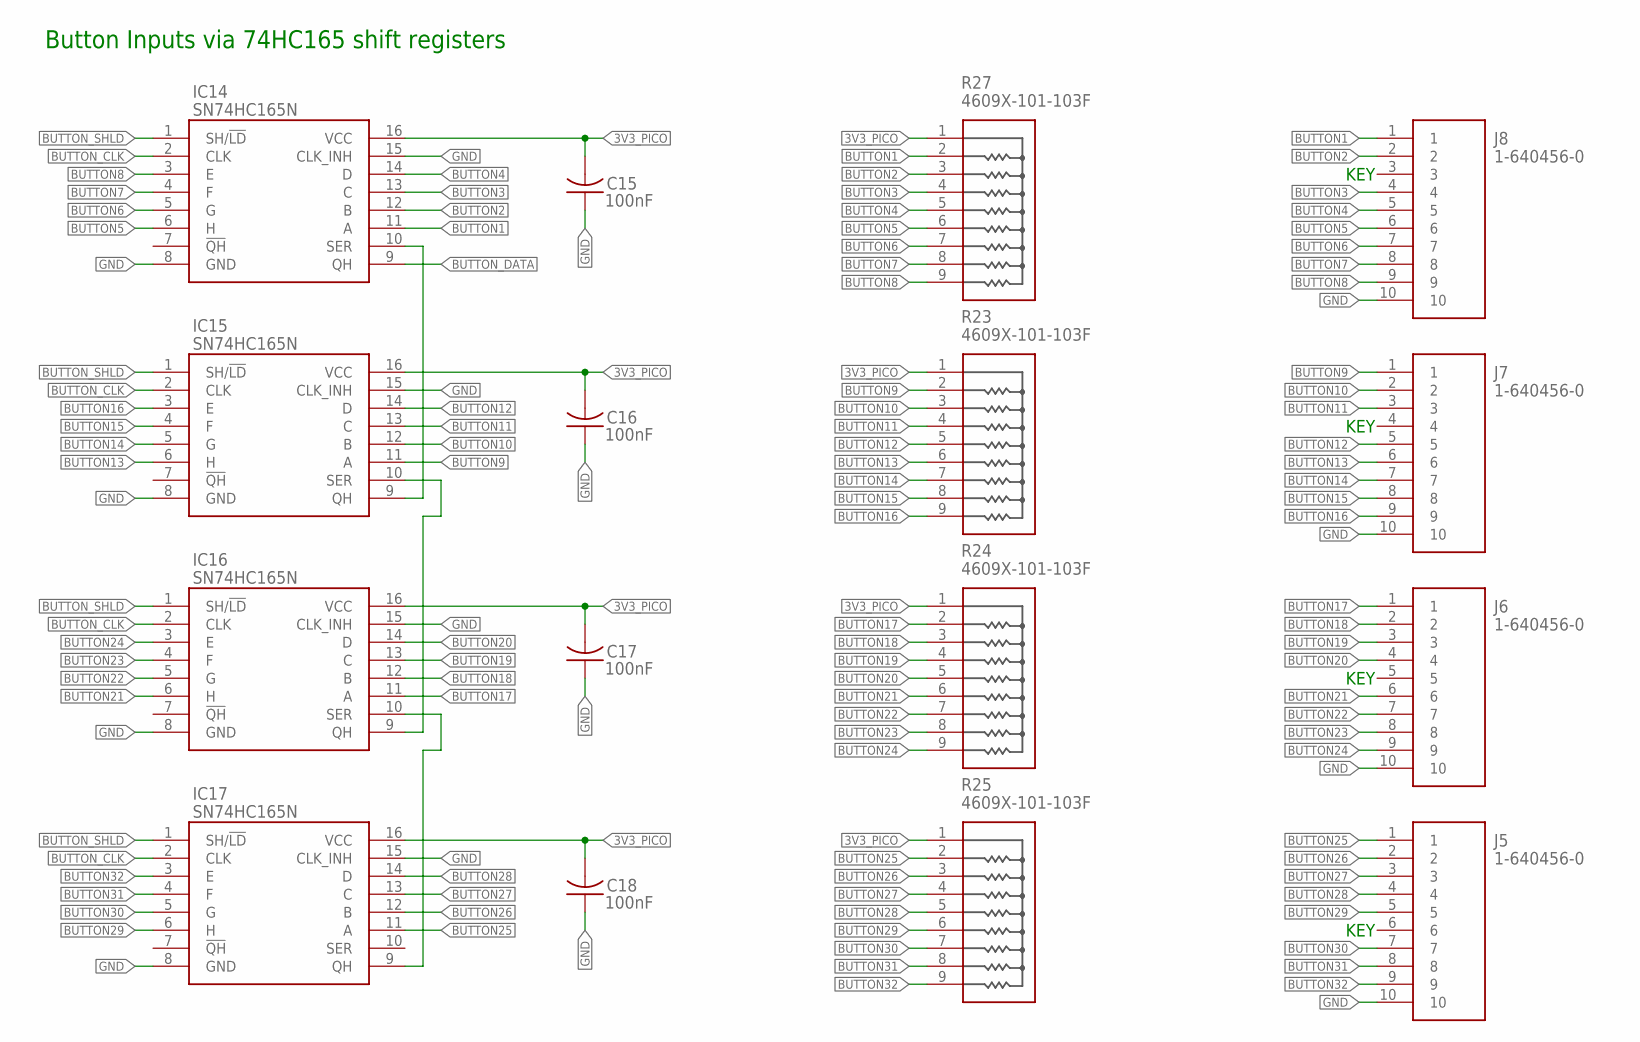
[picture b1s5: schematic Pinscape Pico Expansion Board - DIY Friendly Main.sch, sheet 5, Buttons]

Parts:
C15, C16, C17, C18: 100nF; C025-024X044; PARTNO K104K15X7RF5TL2
IC14, IC15, IC16, IC17: SN74HC165N; DIP794W53P254L1930H508Q16N
J5, J6, J7, J8: 1-640456-0; SHDR10W66P0X254_1X10_2540X572X
R23, R24, R25, R27: 4609X-101-103F; 4609X

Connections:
3V3_PICO: C15.2, C16.2, C17.2, C18.2, IC14.16 (VCC), IC15.16 (VCC), IC16.16 (VCC), IC17.16 (VCC), R23.1, R24.1, R25.1, R27.1; also elsewhere on the board
BUTTON1: IC14.11 (A), J8.1, R27.2
BUTTON2: IC14.12 (B), J8.2, R27.3
BUTTON3: IC14.13 (C), J8.4, R27.4
BUTTON4: IC14.14 (D), J8.5, R27.5
BUTTON5: IC14.6 (H), J8.6, R27.6
BUTTON6: IC14.5 (G), J8.7, R27.7
BUTTON7: IC14.4 (F), J8.8, R27.8
BUTTON8: IC14.3 (E), J8.9, R27.9
BUTTON9: IC15.11 (A), J7.1, R23.2
BUTTON10: IC15.12 (B), J7.2, R23.3
BUTTON11: IC15.13 (C), J7.3, R23.4
BUTTON12: IC15.14 (D), J7.5, R23.5
BUTTON13: IC15.6 (H), J7.6, R23.6
BUTTON14: IC15.5 (G), J7.7, R23.7
BUTTON15: IC15.4 (F), J7.8, R23.8
BUTTON16: IC15.3 (E), J7.9, R23.9
BUTTON17: IC16.11 (A), J6.1, R24.2
BUTTON18: IC16.12 (B), J6.2, R24.3
BUTTON19: IC16.13 (C), J6.3, R24.4
BUTTON20: IC16.14 (D), J6.4, R24.5
BUTTON21: IC16.6 (H), J6.6, R24.6
BUTTON22: IC16.5 (G), J6.7, R24.7
BUTTON23: IC16.4 (F), J6.8, R24.8
BUTTON24: IC16.3 (E), J6.9, R24.9
BUTTON25: IC17.11 (A), J5.1, R25.2
BUTTON26: IC17.12 (B), J5.2, R25.3
BUTTON27: IC17.13 (C), J5.3, R25.4
BUTTON28: IC17.14 (D), J5.4, R25.5
BUTTON29: IC17.6 (H), J5.5, R25.6
BUTTON30: IC17.5 (G), J5.7, R25.7
BUTTON31: IC17.4 (F), J5.8, R25.8
BUTTON32: IC17.3 (E), J5.9, R25.9
BUTTON_CLK: IC14.2 (CLK), IC15.2 (CLK), IC16.2 (CLK), IC17.2 (CLK); also elsewhere on the board
BUTTON_DATA: IC14.9 (QH); also elsewhere on the board
BUTTON_SHLD: IC14.1 (SH/!LD), IC15.1 (SH/!LD), IC16.1 (SH/!LD), IC17.1 (SH/!LD); also elsewhere on the board
GND: C15.1, C16.1, C17.1, C18.1, IC14.8 (GND), IC14.15 (CLK_INH), IC15.8 (GND), IC15.15 (CLK_INH), IC16.8 (GND), IC16.15 (CLK_INH), IC17.8 (GND), IC17.15 (CLK_INH), J5.10, J6.10, J7.10, J8.10; also elsewhere on the board
unnamed: IC14.10 (SER), IC15.9 (QH)
unnamed: IC15.10 (SER), IC16.9 (QH)
unnamed: IC16.10 (SER), IC17.9 (QH)

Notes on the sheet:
KEY
Button Inputs via 74HC165 shift registers

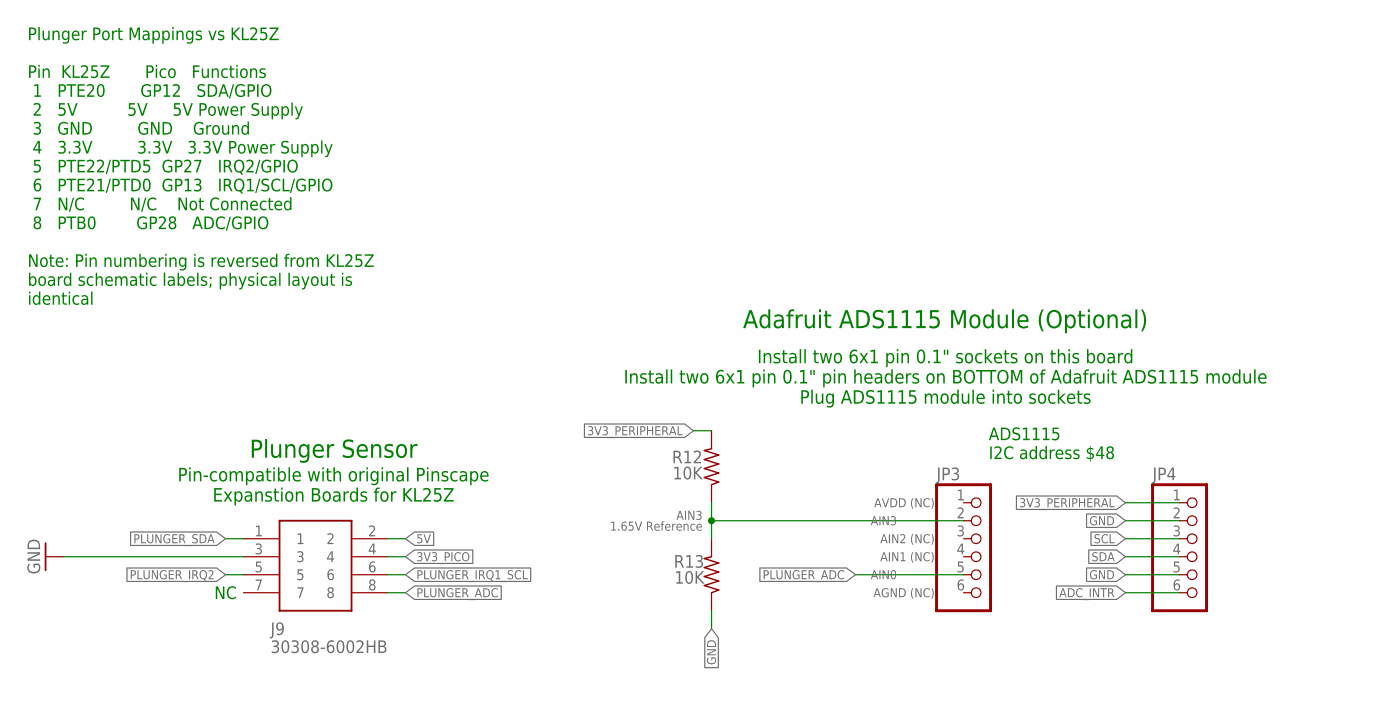
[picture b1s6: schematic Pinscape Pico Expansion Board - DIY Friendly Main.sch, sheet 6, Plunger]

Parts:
J9: 30308-6002HB; SHDR8W69P254_2X4_1780X878X955P
JP3, JP4: PINHD-1X6; 1X06
R12, R13: 10K; 0204/7; PARTNO mfr-12frrf52-10k

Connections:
3V3_PERIPHERAL: JP4.1, R12.2; also elsewhere on the board
3V3_PICO: J9.4; also elsewhere on the board
5V: J9.2; also elsewhere on the board
ADC_INTR: JP4.6; also elsewhere on the board
GND: J9.3, JP4.2, JP4.5, R13.1; also elsewhere on the board
unnamed: JP3.2, R12.1, R13.2
PLUNGER_ADC: J9.8, JP3.5; also elsewhere on the board
PLUNGER_IRQ1_SCL: J9.6; also elsewhere on the board
PLUNGER_IRQ2: J9.5; also elsewhere on the board
PLUNGER_SDA: J9.1; also elsewhere on the board
SCL: JP4.3; also elsewhere on the board
SDA: JP4.4; also elsewhere on the board

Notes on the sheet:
Plunger Sensor
Adafruit ADS1115 Module (Optional)
Install two 6x1 pin 0.1" sockets on this board Install two 6x1 pin 0.1" pin headers on BOTTOM of Adafruit ADS1115 module Plug ADS1115 module into sockets
AVDD (NC)
AGND (NC)
AIN3 1.65V Reference
AIN2 (NC)
AIN1 (NC)
Pin-compatible with original Pinscape Expanstion Boards for KL25Z
ADS1115 I2C address $48
Plunger Port Mappings vs KL25Z Pin KL25Z Pico Functions 1 PTE20 GP12 SDA/GPIO 2 5V 5V 5V Power Supply 3 GND GND Ground 4 3.3V 3.3V 3.3V Power Supply 5 PTE22/PTD5 GP27 IRQ2/GPIO 6 PTE21/PTD0 GP13 IRQ1/SCL/GPIO 7 N/C N/C Not Connected 8 PTB0 GP28 ADC/GPIO Note: Pin numbering is reversed from KL25Z bo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
AIN0
AIN3

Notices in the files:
ExpansionBoards/DIY-Friendly/README.md:
The board schematics and layouts, and all of the associated files and
documentation, are Copyright 2025 Michael J Roberts, and released
under an open source license (BDS 3-clause) with NO WARRANTY.
README.md:
License:
Released under a BSD 3-clause license - NO WARRANTY
CRC++, Copyright (c) 2022, Daniel Bahr.  Distributed under a BSD
Pico C++ SDK, Copyright 2020 by Raspberry Pi (Trading) ltd.
Distributed under a BSD 3-clause license.
Scintlla Edit Control, Copyright 1998-2021 by Neil Hodgson
